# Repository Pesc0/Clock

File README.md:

# Clock
A digital clock based on the AtTiny85 and DS3231 chips.

### Features:
 * Simple interface, designed for the elderly who just need a simple clock.
 * Time is kept even after a power loss, provided the battery is working.
 * Great time keeping accuracy, thanks to the 2ppm accuracy of the DS3231 chip (basically in the worse case it will gain/lose 1 minute every year).
 * Brightness can be adjusted, the value is saved and will be restored even after a complete power loss.
 * Can display ambient temperature (the value is updated internally every minute or so).
 * Easy to build PCB, ideal for beginners.
 * Cheap, around $10.
 * The display consumes most of the power, so in theory it's possible to run the clock on batteries [not tested]. 
 * Fully open source.

## PCB Design
Things to note:
- The board is symmetrical to simplify the design of mounting mechanisms.
- The button panel is "removable" from the main pcb body, to allow repositioning of the buttons.
- On the board are present two jumpers that disconnect the ATTiny from the I2C bus, for debug purposes.

## 3D printed case
TBD

## Building and Flashing the firmware

You will need a working avr toolchain, with `avr-gcc` and `avrdude` installed on your computer. They are very easy to install on a linux computer, but on windows you will have to fiddle with Arduino IDE.
You will also need an AVR programmer, or alternatively you can use "Arduino as ISP". 
You may need to modify the makefile and replace /dev/ttyACM0 with the usb port where your ICSP programmer is connected.

Once the programmer is connected to the board simply run  
``` 
make install 
```

# Gallery

# Revisions
- rev-1: initial design
- rev-2: fix display was upside down, despite silkscreen being right side up

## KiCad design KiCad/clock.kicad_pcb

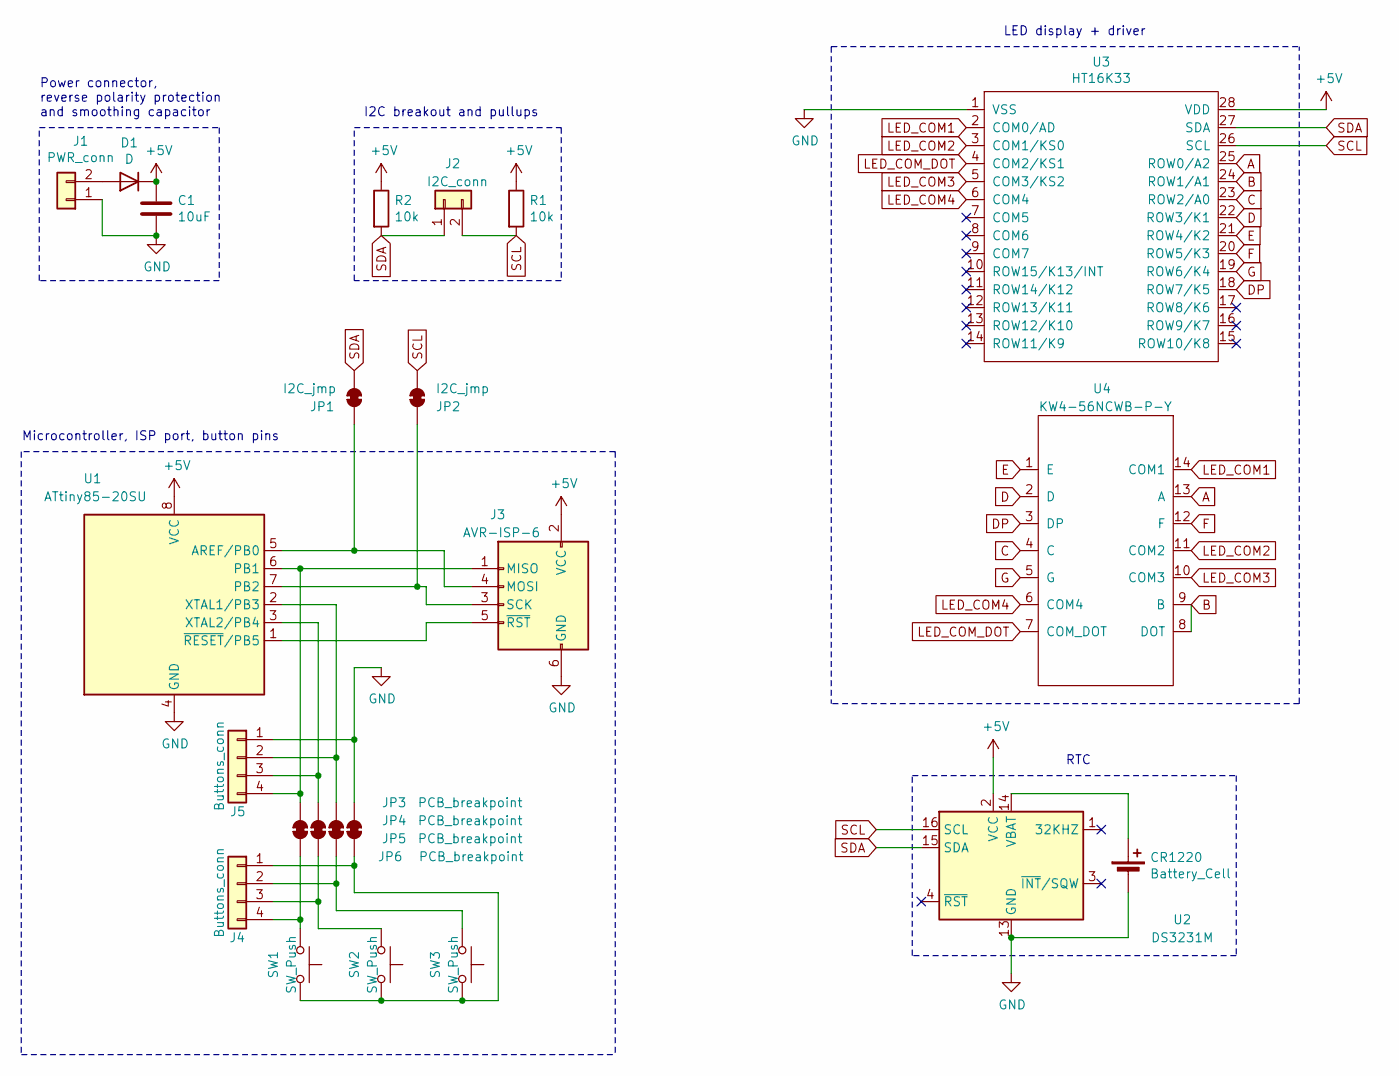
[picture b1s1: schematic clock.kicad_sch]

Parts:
C1: 10uF; C_0805_2012Metric_Pad1.15x1.40mm_HandSolder
CR1220: Battery_Cell; BatteryHolder_Keystone_3001_1x12mm
D1: D; D_0805_2012Metric_Pad1.15x1.40mm_HandSolder
J1: PWR_conn; PinHeader_1x02_P2.54mm_Vertical
J2: I2C_conn; PinHeader_1x02_P2.54mm_Vertical
J3: AVR-ISP-6; PinHeader_2x03_P2.54mm_Vertical
J4, J5: Buttons_conn; PinHeader_1x04_P2.54mm_Vertical
JP1, JP2: I2C_jmp; SolderJumper-2_P1.3mm_Bridged_RoundedPad1.0x1.5mm
JP3, JP4, JP5, JP6: PCB_breakpoint; SolderJumper-2_P1.3mm_Bridged_RoundedPad1.0x1.5mm
R1, R2: 10k; R_0805_2012Metric_Pad1.15x1.40mm_HandSolder
SW1, SW2, SW3: SW_Push; SW_PUSH_6mm
U1: ATtiny85-20SU; SOIJ-8_5.3x5.3mm_P1.27mm
U2: DS3231M; SOIC-16W_7.5x10.3mm_P1.27mm
U3: HT16K33
U4: KW4-56NCWB-P-Y; 7segment

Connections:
+5V: C1.1, D1.1 (K), J3.2 (VCC), R1.1, R2.1, U1.8 (VCC), U2.2 (VCC), U3.28 (VDD)
A: U3.25 (ROW0/A2), U4.13 (A)
B: U3.24 (ROW1/A1), U4.8 (DOT), U4.9 (B)
C: U3.23 (ROW2/A0), U4.4 (C)
D: U3.22 (ROW3/K1), U4.2 (D)
DP: U3.18 (ROW7/K5), U4.3 (DP)
E: U3.21 (ROW4/K2), U4.1 (E)
F: U3.20 (ROW5/K3), U4.12 (F)
G: U3.19 (ROW6/K4), U4.5 (G)
GND: C1.2, CR1220.2 (-), J1.1, J3.6 (GND), J5.1, JP6.1 (A), U1.4 (GND), U2.5 (GND), U2.6 (GND), U2.7 (GND), U2.8 (GND), U2.9 (GND), U2.10 (GND), U2.11 (GND), U2.12 (GND), U2.13 (GND), U3.1 (VSS)
LED_COM1: U3.2 (COM0/AD), U4.14 (COM1)
LED_COM2: U3.3 (COM1/KS0), U4.11 (COM2)
LED_COM3: U3.5 (COM3/KS2), U4.10 (COM3)
LED_COM4: U3.6 (COM4), U4.6 (COM4)
LED_COM_DOT: U3.4 (COM2/KS1), U4.7 (COM_DOT)
unnamed: CR1220.1 (+), U2.14 (VBAT)
unnamed: D1.2 (A), J1.2
unnamed: J3.1 (MISO), J5.4, JP3.1 (A), U1.6 (PB1)
unnamed: J3.3 (SCK), JP2.2 (B), U1.7 (PB2)
unnamed: J3.4 (MOSI), JP1.2 (B), U1.5 (AREF/PB0)
unnamed: J3.5 (~RST), U1.1 (~RESET/PB5)
unnamed: J4.1, JP6.2 (B), SW1.2, SW2.2, SW3.2
unnamed: J4.2, JP5.2 (B), SW3.1
unnamed: J4.3, JP4.2 (B), SW2.1
unnamed: J4.4, JP3.2 (B), SW1.1
unnamed: J5.2, JP5.1 (A), U1.2 (XTAL1/PB3)
unnamed: J5.3, JP4.1 (A), U1.3 (XTAL2/PB4)
SCL: J2.2, JP2.1 (A), R1.2, U2.16 (SCL), U3.26 (SCL)
SDA: J2.1, JP1.1 (A), R2.2, U2.15 (SDA), U3.27 (SDA)

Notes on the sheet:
Microcontroller, ISP port, button pins
I2C breakout and pullups
RTC
LED display + driver
Power connector, reverse polarity protection and smoothing capacitor

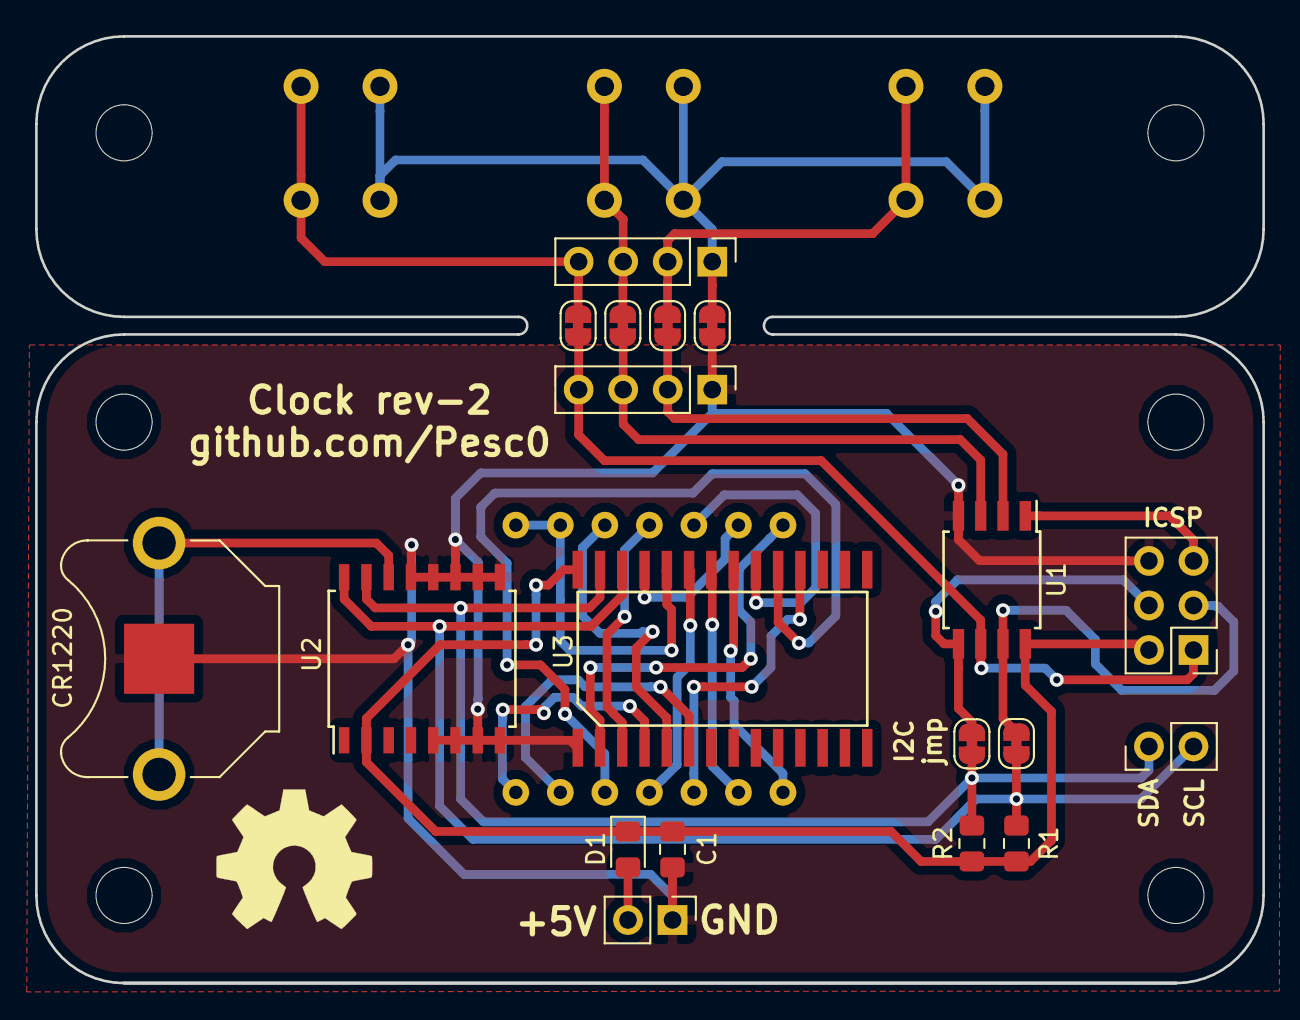
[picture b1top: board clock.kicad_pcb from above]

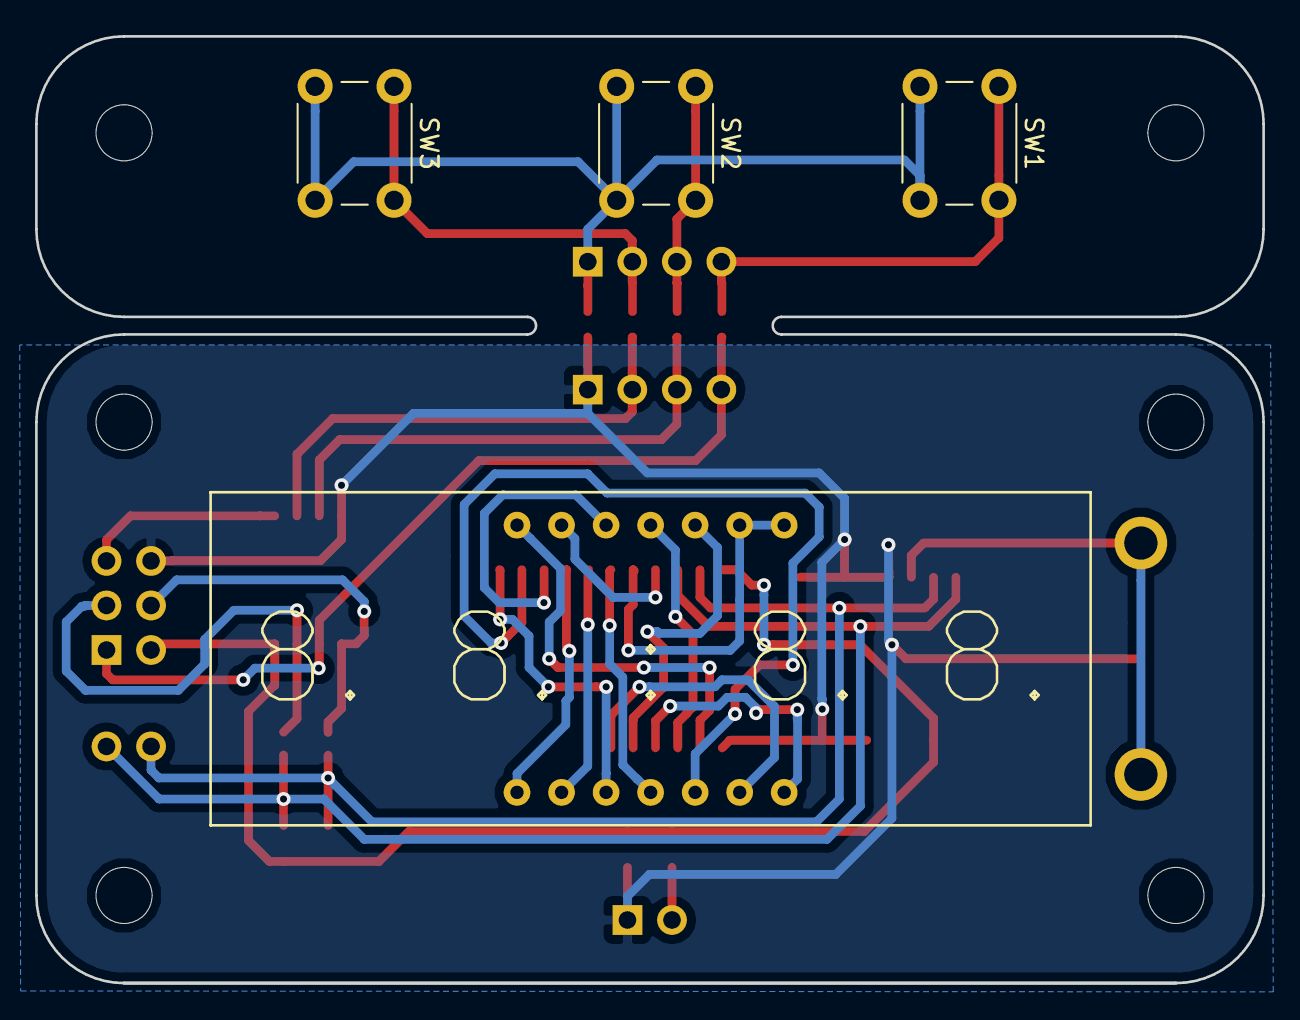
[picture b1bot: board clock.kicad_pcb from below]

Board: 2 copper layers, 70.0 x 54.0 mm, 23 parts (4 on the bottom side), 29 nets.

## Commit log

2020-03-04 repo reorganization
2020-03-28 some upgrades
2020-04-15 config comments
2020-06-25 added gitignore
2020-06-25 updated makefile
2020-06-25 Updated gitignore
2020-06-25 refactoring
2020-06-25 bugfix
2021-06-23 Added PCB Files
2021-06-23 moved gerber files
2024-03-21 Update kicad version
2024-03-21 Add images to readme
2024-03-21 add note about revisions
